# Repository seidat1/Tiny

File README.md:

<h1>Tiny</h1>
<h2>COMP JU+TE R</h2>
<h3><a href="https://hc-ddr.hucki.net/wiki/lib/exe/fetch.php/tiny:jutecomp1.pdf">Zeitschrift Jugend und Technik 1988</a></h3>
<h3><a href="https://hc-ddr.hucki.net/wiki/lib/exe/fetch.php/tiny/buch.pdf">Buch Tiny</a></h3>
<a target=""

<p>
Schlagworte: Tiny, Comp JU+TE r, DDR, 1988, Jugend und Technik, Zeitschrift, Rechner, Computer, 4k
</p>

<p>
Auch 35 Jahre nach Erscheinen der Artikel in des Zeitschrift Jugend und Technik werden noch "COMP JU+TE R" gebaut.
 Mir sind 2 Fälle bekannt. Beide Geräte sind lauffähig und beruhen auf der 4k-Version. Grundlage war die
 Anleitung im Buch "Tiny".
</p>

<p>
In meinem Gerät kamen Speichermodule vom Typ C zum Einsatz. Diese Steckkarte lässt sich mit 8k RAM und 8k
 EPROM bestücken. Zusätzlich wurde eine weitere Karte vom Typ C verbaut, die nur mit 8kByte RAM bestückt ist.
 Somit stehen 16k RAM zur Verfügung. Davon muss der Bildspeicher abgezogen werden.<br />
Im Gerät befindet sich eine 3. Steckkarte, auf der ein 512kByte ROM verbaut ist. Um den Adressbereich zu erweitern,
 wurde ein Zähler eingesetzt. Dieser ROM wird als ROM-Bank benutzt und beherbergt eine Datenbank mit Programmen
 für dieses Gerät.<br />
Verzichtet wurde bei meinem Gerät auf Erweiterungen, wie Tonbandanschluss und mehr.
</p>

### Bilderverzeichnis:

<p>
  <table border="0">
<!-- ------------------------------ -->
    <tr>
      <td>
        
      </td>
      <td>
        <ul>
          <li>Vorderansicht</li>
        </ul>
      </td>
    </tr>
<!-- ------------------------------ -->
    <tr>
      <td>
        
      </td>
      <td>
        <ul>
          <li>Ansicht vorne links</li>
        </ul>
      </td>
    </tr>
<!-- ------------------------------ -->
    <tr>
      <td>
        
      </td>
      <td>
        <ul>
          <li>Ansicht vorne oben</li>
        </ul>
      </td>
    </tr>
<!-- ------------------------------ -->
    <tr>
      <td>
        
      </td>
      <td>
        <ul>
          <li>Startbild</li>
        </ul>
      </td>
    </tr>
<!-- ------------------------------ -->
    <tr>
      <td>
        
      </td>
      <td>
        <ul>
          <li>Turm von Hanoi</li>
        </ul>
      </td>
    </tr>
<!-- ------------------------------ -->
    <tr>
      <td>
        
      </td>
      <td>
        <ul>
          <li>Netzanschluss Hohlbuchse 2,1/5,5</li>
          <li>Resettaster</li>
          <li>Compositanschluss</li>
        </ul>
      </td>
    </tr>
<!-- ------------------------------ -->
    <tr>
      <td>
        
      </td>
      <td>
        <ul>
          <li>Innenansicht von hinten</li>
        </ul>
      </td>
    </tr>
<!-- ------------------------------ -->
    <tr>
      <td>
        
      </td>
      <td>
        <ul>
          <li>Innenansicht von vorn oben</li>
        </ul>
      </td>
    </tr>
<!-- ------------------------------ -->
    <tr>
      <td>
        
      </td>
      <td>
        <ul>
          <li>Speicherkarten</li>
        </ul>
      </td>
    </tr>
<!-- ------------------------------ -->
    <tr>
      <td>
        
      </td>
      <td>
        <ul>
          <li>Platinenhalter</li>
        </ul>
      </td>
    </tr>
<!-- ------------------------------ -->
    <tr>
      <td>
        
      </td>
      <td>
        <ul>
          <li>Prozessor L&uuml;fter</li>
        </ul>
      </td>
    </tr>
<!-- ------------------------------ -->
    <tr>
      <td>
        
      </td>
      <td>
        <ul>
          <li>Hauptleiterplatte</li>
        </ul>
      </td>
    </tr>
<!-- ------------------------------ -->
    <tr>
      <td>
        
      </td>
      <td>
        <ul>
          <li>Leiterplatte Tastatur</li>
        </ul>
      </td>
    </tr>
<!-- ------------------------------ -->
    <tr>
      <td>
        
      </td>
      <td>
        <ul>
          <li>Leiterplatte ROM RAM</li>
        </ul>
      </td>
    </tr>
<!-- ------------------------------ -->
    <tr>
      <td>
        
      </td>
      <td>
        <ul>
          <li>Leiterplatte ROM BANK</li>
        </ul>
      </td>
    </tr>
<!-- ------------------------------ -->
    <tr>
      <td>
        
      </td>
      <td>
        <ul>
          <li>UB8821 Best&uuml;ckungsseite</li>
        </ul>
      </td>
    </tr>
<!-- ------------------------------ -->
    <tr>
      <td>
        
      </td>
      <td>
        <ul>
          <li>UB8821 Leiterseite</li>
        </ul>
      </td>
    </tr>
<!-- ------------------------------ -->
  </table>
</p>

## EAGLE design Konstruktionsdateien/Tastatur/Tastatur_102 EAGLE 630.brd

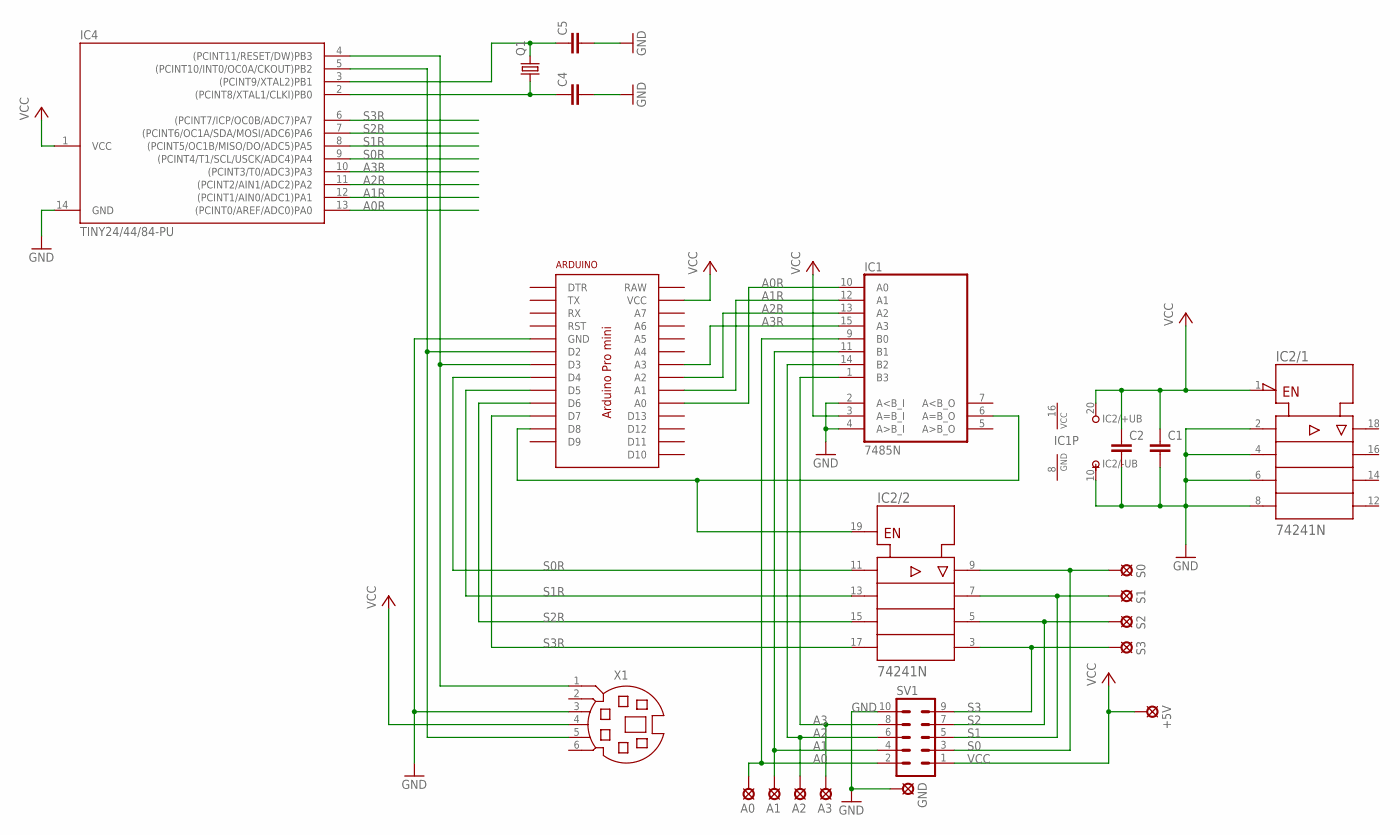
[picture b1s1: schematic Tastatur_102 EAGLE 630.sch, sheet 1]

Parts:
+5V: MCS10B
A0, A1, A2, A3: MCS10B
ARDUINO: ARDUINO_PRO_MINIARDUINO_PRO_MINI_8; ARDUINO_PRO_MINI_8
C1, C2, C4, C5: C-EU025-024X044; C025-024X044
GND: MCS10B
IC1: 7485N; DIL16
IC2: 74241N; DIL20
IC4: TINY24/44/84-PU; DIL14
Q1: CRYSTALHC49U-V; HC49U-V
S0, S1, S2, S3: MCS10B
SV1: ML10
X1: MD06SSMDIN06L; MDIN06SSL

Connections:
A0: A0.MP, IC1.9 (B0), SV1.2; also elsewhere on the board
A0R: ARDUINO.A0, IC1.10 (A0), IC4.13 ((PCINT0/AREF/ADC0)PA0)
A1: A1.MP, IC1.11 (B1), SV1.4; also elsewhere on the board
A1R: ARDUINO.A1, IC1.12 (A1), IC4.12 ((PCINT1/AIN0/ADC1)PA1)
A2: A2.MP, IC1.14 (B2), SV1.6; also elsewhere on the board
A2R: ARDUINO.A2, IC1.13 (A2), IC4.11 ((PCINT2/AIN1/ADC2)PA2)
A3: A3.MP, IC1.1 (B3), SV1.8; also elsewhere on the board
A3R: ARDUINO.A3, IC1.15 (A3), IC4.10 ((PCINT3/T0/ADC3)PA3)
GND: ARDUINO.GND, ARDUINO.GND@1 (GND), C1.2, C2.2, C4.2, C5.2, GND.MP, IC1.2 (A<B_I), IC1.4 (A>B_I), IC1.8 (GND), IC2.2 (A1), IC2.4 (A2), IC2.6 (A3), IC2.8 (A4), IC2.10 (-UB), IC4.14 (GND), SV1.10, X1.3; also elsewhere on the board
unnamed: ARDUINO.D2, IC4.5 ((PCINT10/INT0/OC0A/CKOUT)PB2), X1.5
unnamed: ARDUINO.D3, IC4.4 ((PCINT11/RESET/DW)PB3), X1.1
unnamed: C4.1, IC4.2 ((PCINT8/XTAL1/CLKI)PB0), Q1.1
unnamed: C5.1, IC4.3 ((PCINT9/XTAL2)PB1), Q1.2
unnamed: ARDUINO.D8, IC1.6 (A=B_O), IC2.19 (G)
S0: IC2.9 (Y1), S0.MP, SV1.3; also elsewhere on the board
S0R: ARDUINO.D4, IC2.11 (A1), IC4.9 ((PCINT4/T1/SCL/USCK/ADC4)PA4)
S1: IC2.7 (Y2), S1.MP, SV1.5; also elsewhere on the board
S1R: ARDUINO.D5, IC2.13 (A2), IC4.8 ((PCINT5/OC1B/MISO/DO/ADC5)PA5)
S2: IC2.5 (Y3), S2.MP, SV1.7; also elsewhere on the board
S2R: ARDUINO.D6, IC2.15 (A3), IC4.7 ((PCINT6/OC1A/SDA/MOSI/ADC6)PA6)
S3: IC2.3 (Y4), S3.MP, SV1.9; also elsewhere on the board
S3R: ARDUINO.D7, IC2.17 (A4), IC4.6 ((PCINT7/ICP/OC0B/ADC7)PA7)
VCC: +5V.MP, ARDUINO.VCC, C1.1, C2.1, IC1.3 (A=B_I), IC1.16 (VCC), IC2.1 (!G), IC2.20 (+UB), IC4.1 (VCC), SV1.1, X1.4; also elsewhere on the board

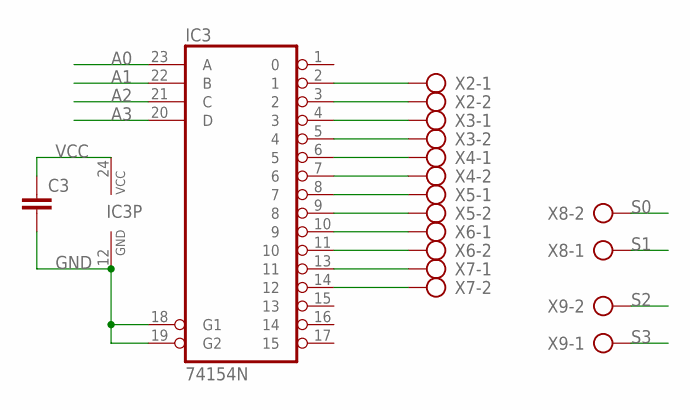
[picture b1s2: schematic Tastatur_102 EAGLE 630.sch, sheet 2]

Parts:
C3: C-EU025-024X044; C025-024X044
IC3: 74154N; DIL24-6
X2, X3, X4, X5, X6, X7, X8, X9: AK500/2

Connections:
A0: IC3.23 (A); also elsewhere on the board
A1: IC3.22 (B); also elsewhere on the board
A2: IC3.21 (C); also elsewhere on the board
A3: IC3.20 (D); also elsewhere on the board
GND: C3.2, IC3.12 (GND), IC3.18 (G1), IC3.19 (G2); also elsewhere on the board
unnamed: IC3.2 (1), X2.1
unnamed: IC3.3 (2), X2.2
unnamed: IC3.4 (3), X3.1
unnamed: IC3.5 (4), X3.2
unnamed: IC3.6 (5), X4.1
unnamed: IC3.7 (6), X4.2
unnamed: IC3.8 (7), X5.1
unnamed: IC3.9 (8), X5.2
unnamed: IC3.10 (9), X6.1
unnamed: IC3.11 (10), X6.2
unnamed: IC3.13 (11), X7.1
unnamed: IC3.14 (12), X7.2
S0: X8.2; also elsewhere on the board
S1: X8.1; also elsewhere on the board
S2: X9.2; also elsewhere on the board
S3: X9.1; also elsewhere on the board
VCC: C3.1, IC3.24 (VCC); also elsewhere on the board

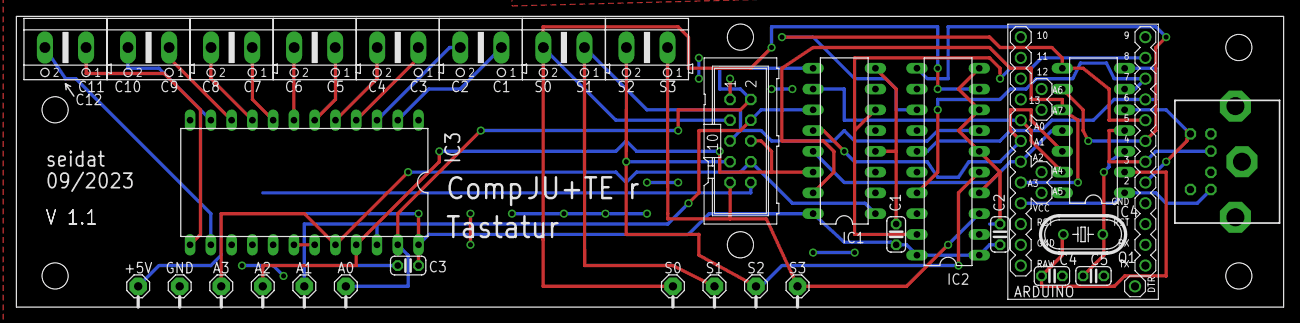
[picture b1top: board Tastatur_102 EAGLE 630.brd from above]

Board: 2 copper layers, 155.0 x 35.6 mm, 31 parts (0 on the bottom side), 35 nets.

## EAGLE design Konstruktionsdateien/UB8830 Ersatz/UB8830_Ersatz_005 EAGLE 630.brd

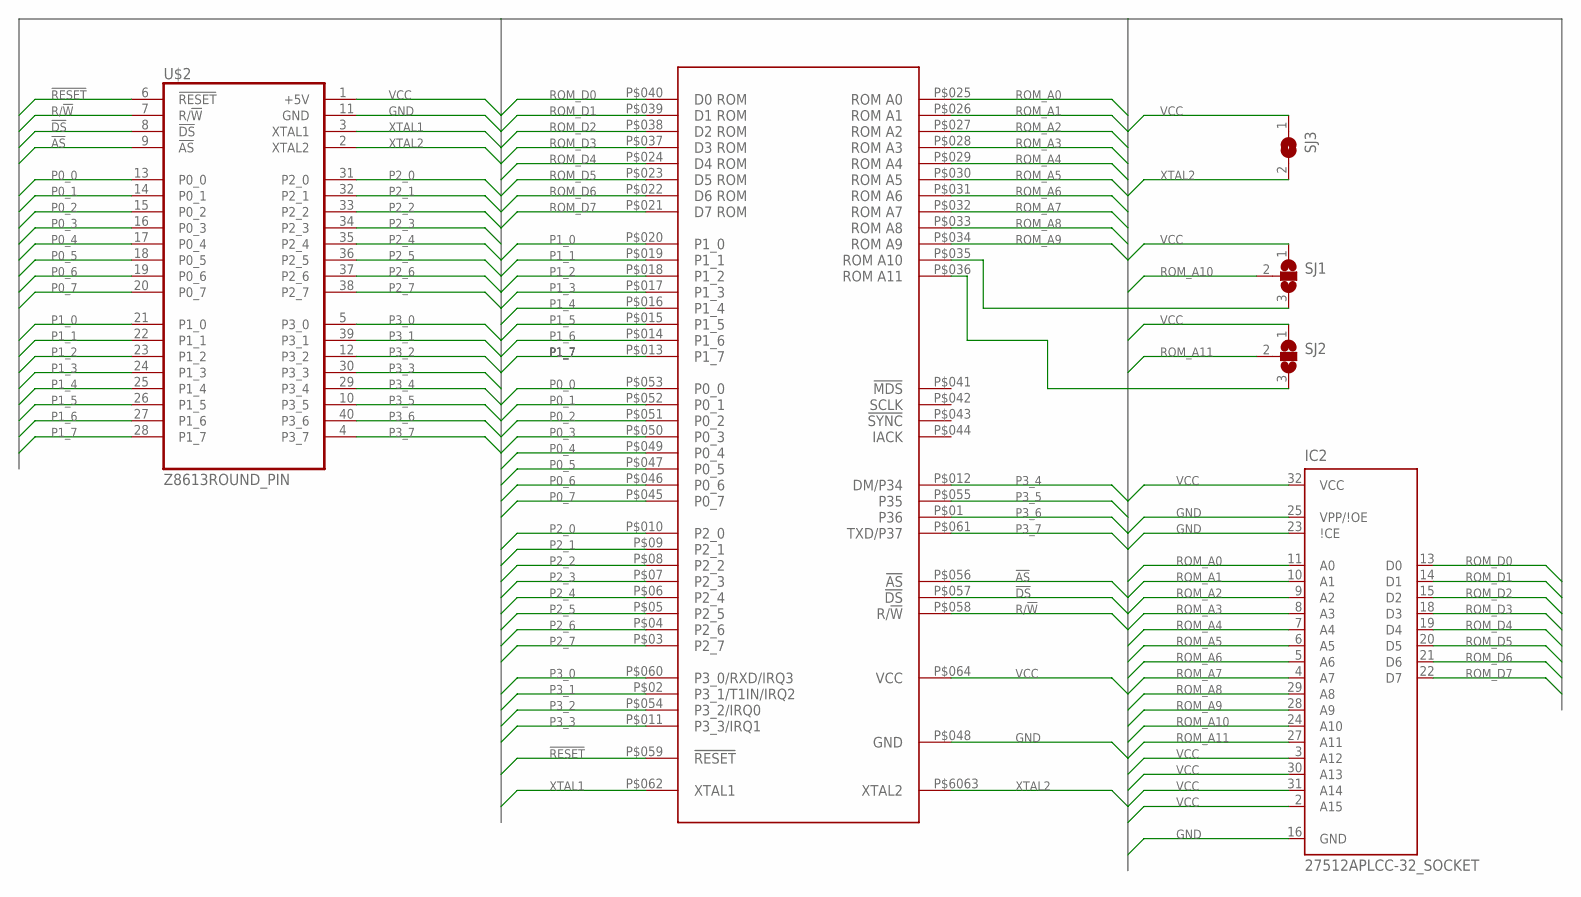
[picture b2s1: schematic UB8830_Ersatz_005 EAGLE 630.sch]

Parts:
IC2: 27512APLCC-32_SOCKET; PLCC-32_SOCKET
SJ1, SJ2: SJ2WSJ_2B; SJ_2B
SJ3: SJ
U$1: UB8821; QUIT64
U$2: Z8613ROUND_PIN; DIL40_ROUND

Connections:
!AS: U$1.P$056, U$2.9 (!AS)
!DS: U$1.P$057, U$2.8 (!DS)
!RESET: U$1.P$059, U$2.6 (!RESET)
GND: IC2.16 (GND), IC2.23 (\!CE), IC2.25 (VPP/\!OE), U$1.P$048, U$2.11 (GND)
unnamed: SJ1.3, U$1.P$035
unnamed: SJ2.3, U$1.P$036
P0_0: U$1.P$053, U$2.13 (P0_0)
P0_1: U$1.P$052, U$2.14 (P0_1)
P0_2: U$1.P$051, U$2.15 (P0_2)
P0_3: U$1.P$050, U$2.16 (P0_3)
P0_4: U$1.P$049, U$2.17 (P0_4)
P0_5: U$1.P$047, U$2.18 (P0_5)
P0_6: U$1.P$046, U$2.19 (P0_6)
P0_7: U$1.P$045, U$2.20 (P0_7)
P1_0: U$1.P$020, U$2.21 (P1_0)
P1_1: U$1.P$019, U$2.22 (P1_1)
P1_2: U$1.P$018, U$2.23 (P1_2)
P1_3: U$1.P$017, U$2.24 (P1_3)
P1_4: U$1.P$016, U$2.25 (P1_4)
P1_5: U$1.P$015, U$2.26 (P1_5)
P1_6: U$1.P$014, U$2.27 (P1_6)
P1_7: U$1.P$013, U$2.28 (P1_7)
P2_0: U$1.P$010, U$2.31 (P2_0)
P2_1: U$1.P$09, U$2.32 (P2_1)
P2_2: U$1.P$08, U$2.33 (P2_2)
P2_3: U$1.P$07, U$2.34 (P2_3)
P2_4: U$1.P$06, U$2.35 (P2_4)
P2_5: U$1.P$05, U$2.36 (P2_5)
P2_6: U$1.P$04, U$2.37 (P2_6)
P2_7: U$1.P$03, U$2.38 (P2_7)
P3_0: U$1.P$060, U$2.5 (P3_0)
P3_1: U$1.P$02, U$2.39 (P3_1)
P3_2: U$1.P$054, U$2.12 (P3_2)
P3_3: U$1.P$011, U$2.30 (P3_3)
P3_4: U$1.P$012, U$2.29 (P3_4)
P3_5: U$1.P$055, U$2.10 (P3_5)
P3_6: U$1.P$01, U$2.40 (P3_6)
P3_7: U$1.P$061, U$2.4 (P3_7)
R/!W: U$1.P$058, U$2.7 (R/!W)
ROM_A0: IC2.11 (A0), U$1.P$025
ROM_A1: IC2.10 (A1), U$1.P$026
ROM_A2: IC2.9 (A2), U$1.P$027
ROM_A3: IC2.8 (A3), U$1.P$028
ROM_A4: IC2.7 (A4), U$1.P$029
ROM_A5: IC2.6 (A5), U$1.P$030
ROM_A6: IC2.5 (A6), U$1.P$031
ROM_A7: IC2.4 (A7), U$1.P$032
ROM_A8: IC2.29 (A8), U$1.P$033
ROM_A9: IC2.28 (A9), U$1.P$034
ROM_A10: IC2.24 (A10), SJ1.2
ROM_A11: IC2.27 (A11), SJ2.2
ROM_D0: IC2.13 (D0), U$1.P$040
ROM_D1: IC2.14 (D1), U$1.P$039
ROM_D2: IC2.15 (D2), U$1.P$038
ROM_D3: IC2.18 (D3), U$1.P$037
ROM_D4: IC2.19 (D4), U$1.P$024
ROM_D5: IC2.20 (D5), U$1.P$023
ROM_D6: IC2.21 (D6), U$1.P$022
ROM_D7: IC2.22 (D7), U$1.P$021
VCC: IC2.2 (A15), IC2.3 (A12), IC2.30 (A13), IC2.31 (A14), IC2.32 (VCC), SJ1.1, SJ2.1, SJ3.1, U$1.P$064, U$2.1 (+5V)
XTAL1: U$1.P$062, U$2.3 (XTAL1)
XTAL2: SJ3.2, U$1.P$6063, U$2.2 (XTAL2)

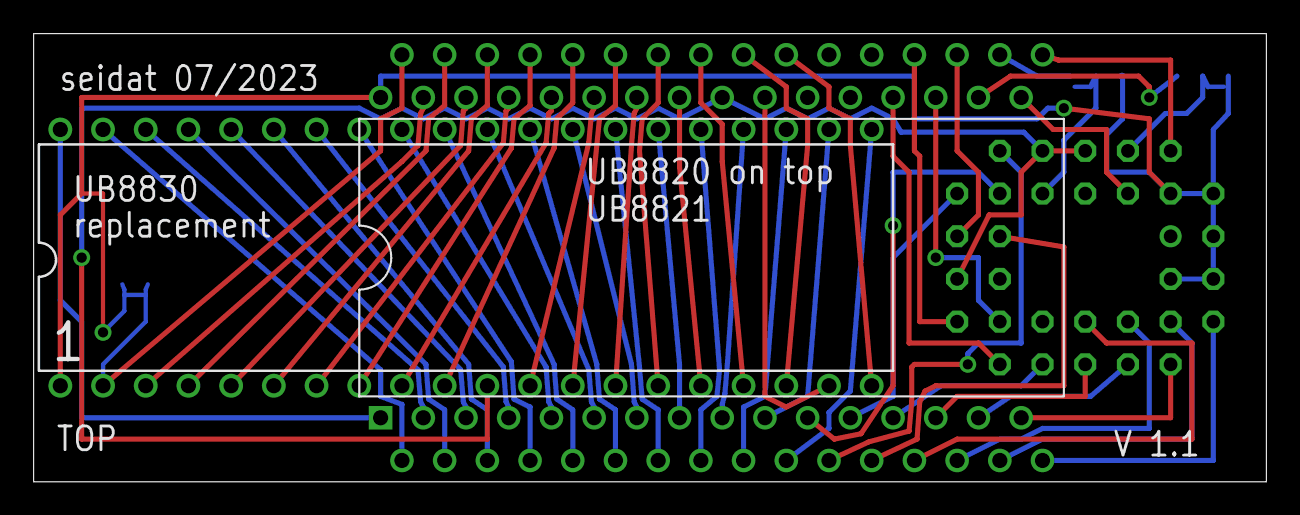
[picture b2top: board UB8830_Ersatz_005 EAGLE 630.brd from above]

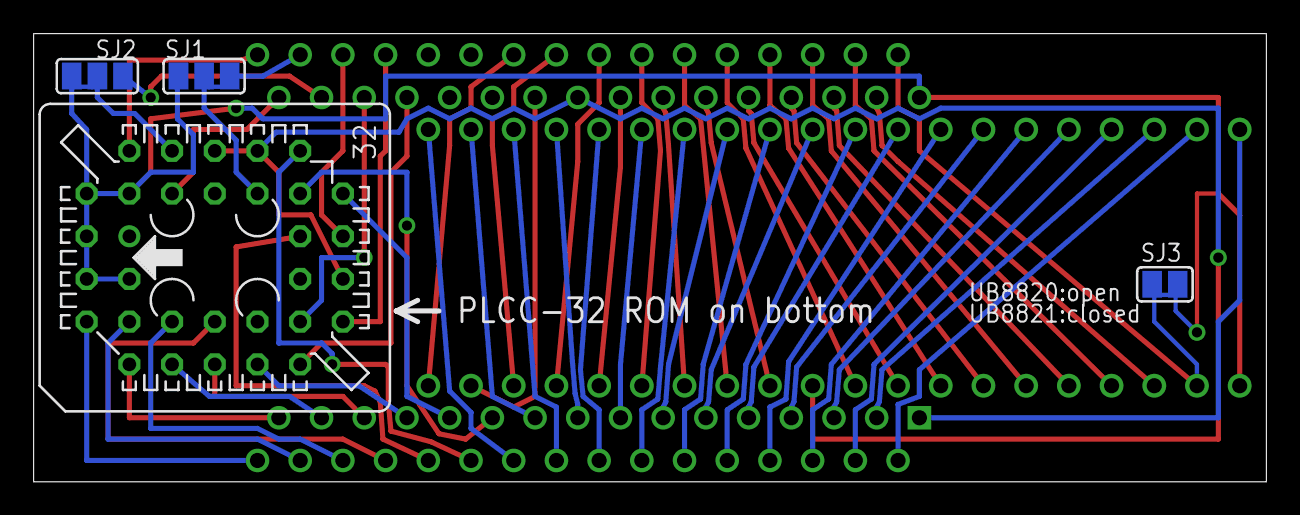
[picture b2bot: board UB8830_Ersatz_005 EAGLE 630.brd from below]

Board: 2 copper layers, 73.3 x 26.7 mm, 6 parts (4 on the bottom side), 62 nets.

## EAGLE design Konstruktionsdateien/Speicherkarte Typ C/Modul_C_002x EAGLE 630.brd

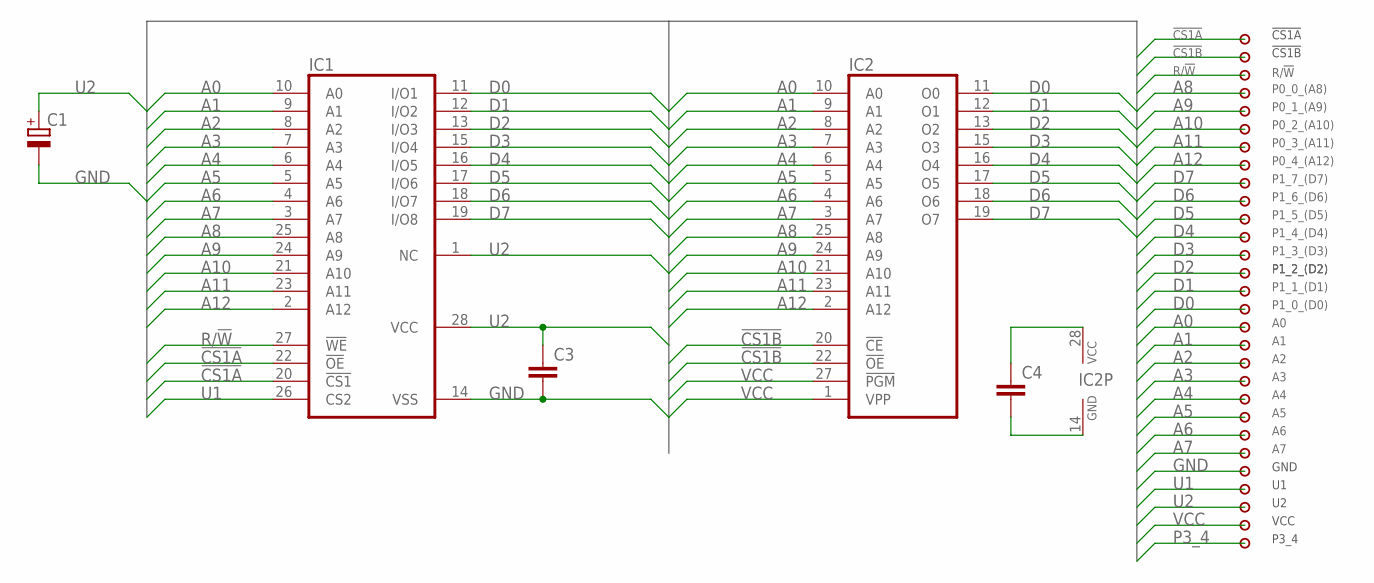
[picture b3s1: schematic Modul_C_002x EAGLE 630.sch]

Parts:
C1: CPOL-EUE15-6AXIAL; E15-6
C3, C4: C-EU025-024X044; C025-024X044
IC1: 6264A; DIL28-6
IC2: 2764; DIL28
U$1: BUS2929PUR; BUS29_PUR

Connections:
!CS1A: IC1.20 (!CS1), IC1.22 (!OE), U$1.1.29
!CS1B: IC2.20 (!CE), IC2.22 (!OE), U$1.1.28
A0: IC1.10 (A0), IC2.10 (A0), U$1.1.13
A1: IC1.9 (A1), IC2.9 (A1), U$1.1.12
A2: IC1.8 (A2), IC2.8 (A2), U$1.1.11
A3: IC1.7 (A3), IC2.7 (A3), U$1.1.10
A4: IC1.6 (A4), IC2.6 (A4), U$1.1.9
A5: IC1.5 (A5), IC2.5 (A5), U$1.1.8
A6: IC1.4 (A6), IC2.4 (A6), U$1.1.7
A7: IC1.3 (A7), IC2.3 (A7), U$1.1.6
A8: IC1.25 (A8), IC2.25 (A8), U$1.1.26
A9: IC1.24 (A9), IC2.24 (A9), U$1.1.25
A10: IC1.21 (A10), IC2.21 (A10), U$1.1.24
A11: IC1.23 (A11), IC2.23 (A11), U$1.1.23
A12: IC1.2 (A12), IC2.2 (A12), U$1.1.22
D0: IC1.11 (I/O1), IC2.11 (O0), U$1.1.14
D1: IC1.12 (I/O2), IC2.12 (O1), U$1.1.15
D2: IC1.13 (I/O3), IC2.13 (O2), U$1.1.16
D3: IC1.15 (I/O4), IC2.15 (O3), U$1.1.17
D4: IC1.16 (I/O5), IC2.16 (O4), U$1.1.18
D5: IC1.17 (I/O6), IC2.17 (O5), U$1.1.19
D6: IC1.18 (I/O7), IC2.18 (O6), U$1.1.20
D7: IC1.19 (I/O8), IC2.19 (O7), U$1.1.21
GND: C1.-, C3.2, C4.2, IC1.14 (VSS), IC2.14 (GND), U$1.1.5
P3_4: U$1.1.1
R/!W: IC1.27 (!WE), U$1.1.27
U1: IC1.26 (CS2), U$1.1.4
U2: C1.+, C3.1, IC1.1 (NC), IC1.28 (VCC), U$1.1.3
VCC: C4.1, IC2.1 (VPP), IC2.27 (!PGM), IC2.28 (VCC), U$1.1.2

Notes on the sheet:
!CS1B
!CS1A
GND
VCC
P3_4

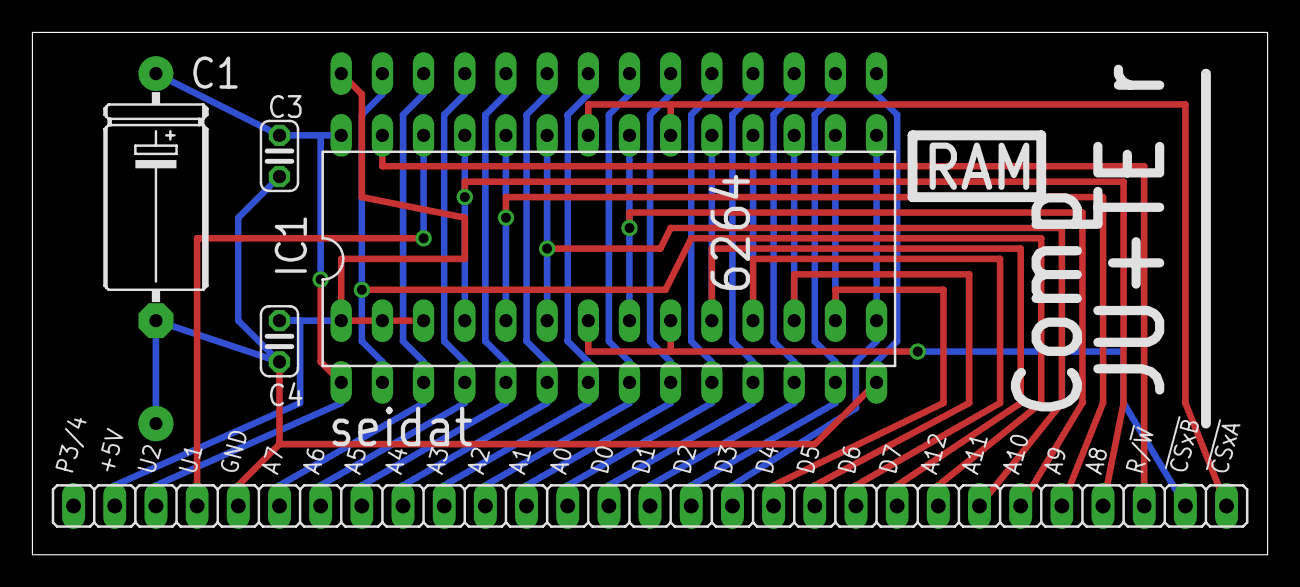
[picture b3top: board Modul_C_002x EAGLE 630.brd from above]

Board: 2 copper layers, 76.2 x 32.2 mm, 6 parts (1 on the bottom side), 28 nets.

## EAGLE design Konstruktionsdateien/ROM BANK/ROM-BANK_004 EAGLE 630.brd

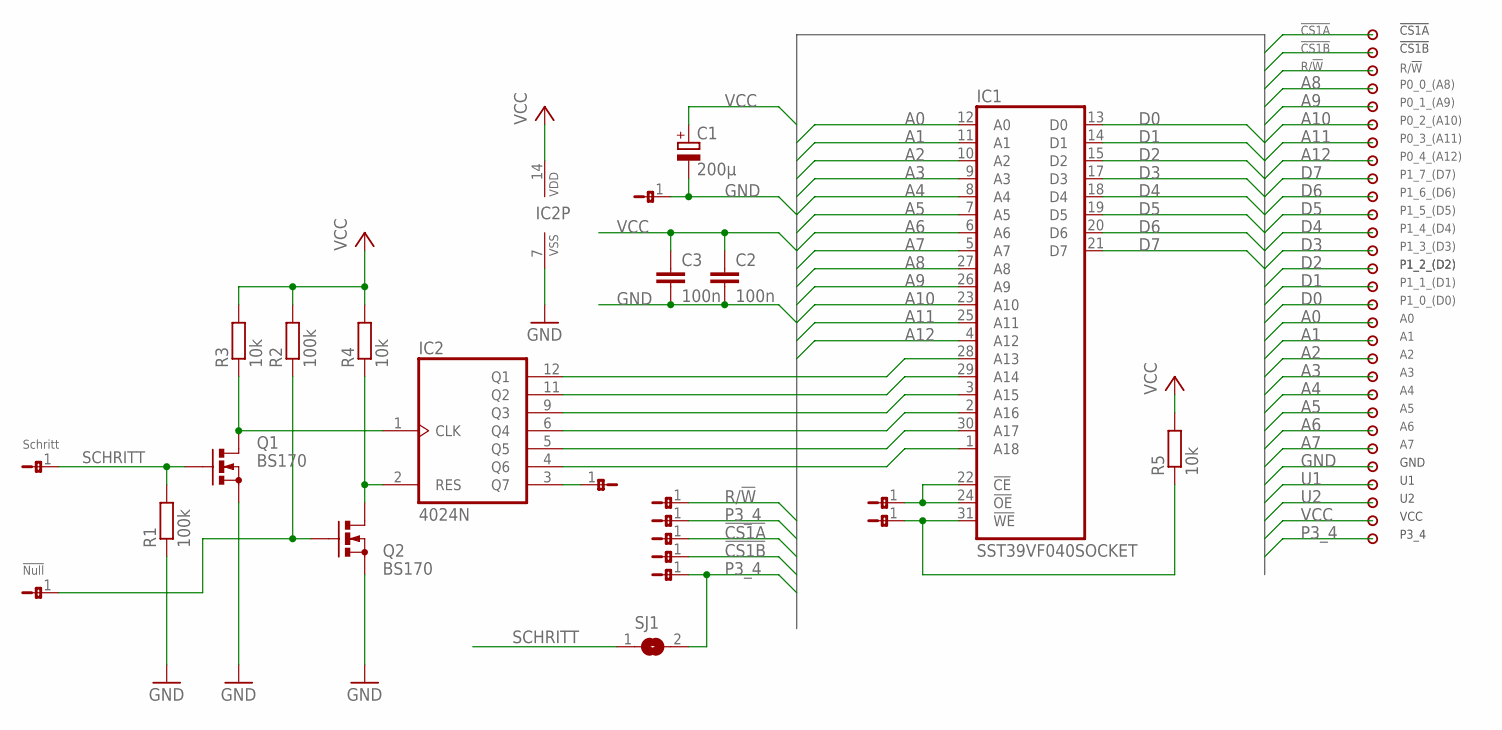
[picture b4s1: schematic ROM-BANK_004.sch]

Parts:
!NULL: JP1-1JP1-1B; JP1-1B
C1: 200µ; E15-6
C2, C3: 100n; C025-024X044
IC1: SST39VF040SOCKET; PLCC-32-SOCKET
IC2: 4024N; DIL14
Q1, Q2: BS170; SOT54E
Q7: JP1-1JP1-1B; JP1-1B
R1, R2: 100k; 0207/10
R3, R4, R5: 10k; 0207/10
R/!W: JP1-1JP1-1B; JP1-1B
SCHRITT: JP1-1JP1-1B; JP1-1B
SJ1: SJ
U$1: BUS2929PUR; BUS29_PUR
U$2, U$3, U$4, U$6, U$8, U$9, U$10: JP1-1JP1-1B; JP1-1B

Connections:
!CE&OE: IC1.22 (!CE), IC1.24 (!OE), U$10.1
!CS1A: U$1.1.29, U$8.1
!CS1B: U$1.1.28, U$9.1
!NULL: !NULL.1, Q2.G, R2.1
!WE: IC1.31 (!WE), R5.1, U$4.1
A0: IC1.12 (A0), U$1.1.13
A1: IC1.11 (A1), U$1.1.12
A2: IC1.10 (A2), U$1.1.11
A3: IC1.9 (A3), U$1.1.10
A4: IC1.8 (A4), U$1.1.9
A5: IC1.7 (A5), U$1.1.8
A6: IC1.6 (A6), U$1.1.7
A7: IC1.5 (A7), U$1.1.6
A8: IC1.27 (A8), U$1.1.26
A9: IC1.26 (A9), U$1.1.25
A10: IC1.23 (A10), U$1.1.24
A11: IC1.25 (A11), U$1.1.23
A12: IC1.4 (A12), U$1.1.22
D0: IC1.13 (D0), U$1.1.14
D1: IC1.14 (D1), U$1.1.15
D2: IC1.15 (D2), U$1.1.16
D3: IC1.17 (D3), U$1.1.17
D4: IC1.18 (D4), U$1.1.18
D5: IC1.19 (D5), U$1.1.19
D6: IC1.20 (D6), U$1.1.20
D7: IC1.21 (D7), U$1.1.21
GND: C1.-, C2.2, C3.2, IC1.16 (GND), IC2.7 (VSS), Q1.S, Q2.S, R1.1, U$1.1.5, U$2.1
unnamed: IC1.28 (A13), IC2.12 (Q1)
unnamed: IC1.29 (A14), IC2.11 (Q2)
unnamed: IC1.3 (A15), IC2.9 (Q3)
unnamed: IC1.2 (A16), IC2.6 (Q4)
unnamed: IC1.30 (A17), IC2.5 (Q5)
unnamed: IC1.1 (A18), IC2.4 (Q6)
unnamed: IC2.2 (RES), Q2.D, R4.1
unnamed: IC2.1 (CLK), Q1.D, R3.1
unnamed: IC2.3 (Q7), Q7.1
P3_4: SJ1.2, U$1.1.1, U$3.1, U$6.1
R/!W: R/!W.1, U$1.1.27
SCHRITT: Q1.G, R1.2, SCHRITT.1, SJ1.1
U1: U$1.1.4
U2: U$1.1.3
VCC: C1.+, C2.1, C3.1, IC1.32 (VCC), IC2.14 (VDD), R2.2, R3.2, R4.2, R5.2, U$1.1.2

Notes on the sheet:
!CS1B
!CS1A
GND
VCC
P3_4
Schritt
!Null

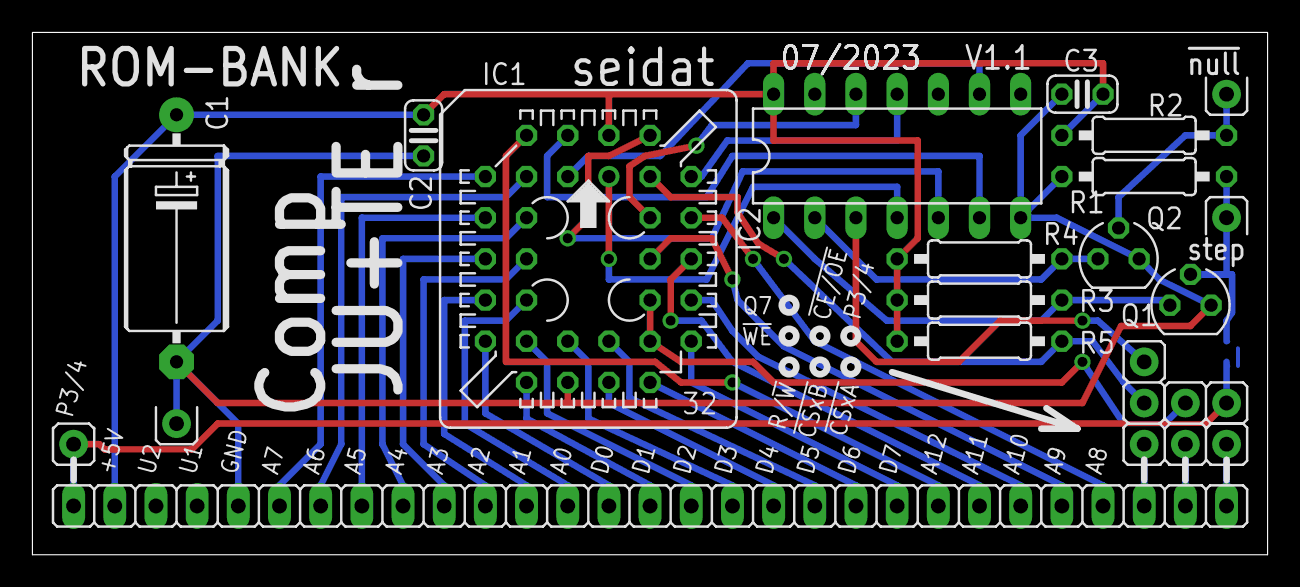
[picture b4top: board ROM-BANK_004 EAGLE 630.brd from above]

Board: 2 copper layers, 76.2 x 32.2 mm, 25 parts (1 on the bottom side), 40 nets.

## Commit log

2023-10-19 no message
